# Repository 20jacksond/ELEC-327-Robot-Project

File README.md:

# ELEC-327-Robot-Project
Repository for the C code (for robot control), Python code (for computer vision), and associated PCB files and other design documents.

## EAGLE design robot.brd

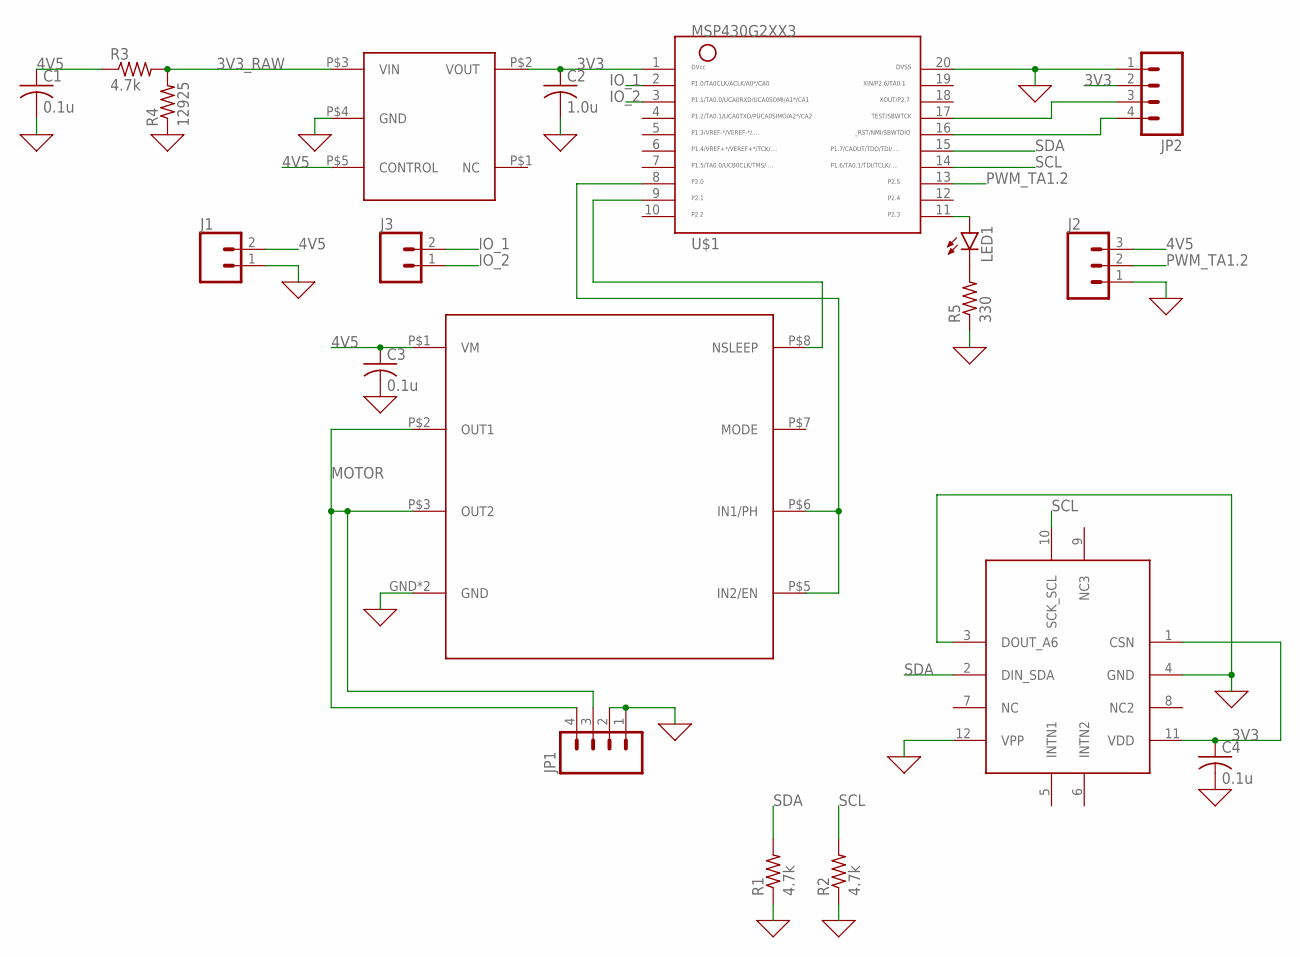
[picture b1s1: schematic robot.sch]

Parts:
C1, C3, C4: 0.1u; C0805
C2: 1.0u; C0805
J1, J3: CONN_02; 1X02
J2: CONN_03LOCK; 1X03_LOCK
JP1, JP2: HEADER_1X04LOCK; 1X04_LOCK
LED1: LED5MM
R1, R2, R3: 4.7k; R0805
R4: 12925; R0805
R5: 330; R0805
U$1: MSP430G2XX3PDIP; N20
U$2: DRV8220_H_BRIDGE
U$4: TCR2EF3V3
U$5: MC3419VFLGA-12; IC_MXC6655XA

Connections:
0: C1.2, C2.2, C3.2, C4.2, J1.1, J2.1, JP1.1, JP1.2, JP2.1, R1.1, R2.1, R4.1, R5.1, U$1.20, U$2.GND, U$2.P$4 (GND), U$4.P$4 (GND), U$5.3 (DOUT_A6), U$5.4 (GND), U$5.12 (VPP)
3V3: C2.1, C4.1, JP2.2, U$1.1, U$4.P$2 (VOUT), U$5.1 (CSN), U$5.11 (VDD)
3V3_RAW: R3.2, R4.2, U$4.P$3 (VIN)
4V5: C1.1, C3.1, J1.2, J2.3, R3.1, U$2.P$1 (VM), U$4.P$5 (CONTROL)
IO_1: J3.2, U$1.2
IO_2: J3.1, U$1.3
MOTOR: JP1.3, JP1.4, U$2.P$2 (OUT1), U$2.P$3 (OUT2)
unnamed: LED1.A, U$1.11
unnamed: U$1.9, U$2.P$8 (NSLEEP)
unnamed: LED1.K (C), R5.2
unnamed: U$1.8, U$2.P$5 (IN2/EN), U$2.P$6 (IN1/PH)
unnamed: JP2.3, U$1.17
unnamed: JP2.4, U$1.16
PWM_TA1.2: J2.2, U$1.13
SCL: R2.2, U$1.14, U$5.10 (SCK_SCL)
SDA: R1.2, U$1.15, U$5.2 (DIN_SDA)

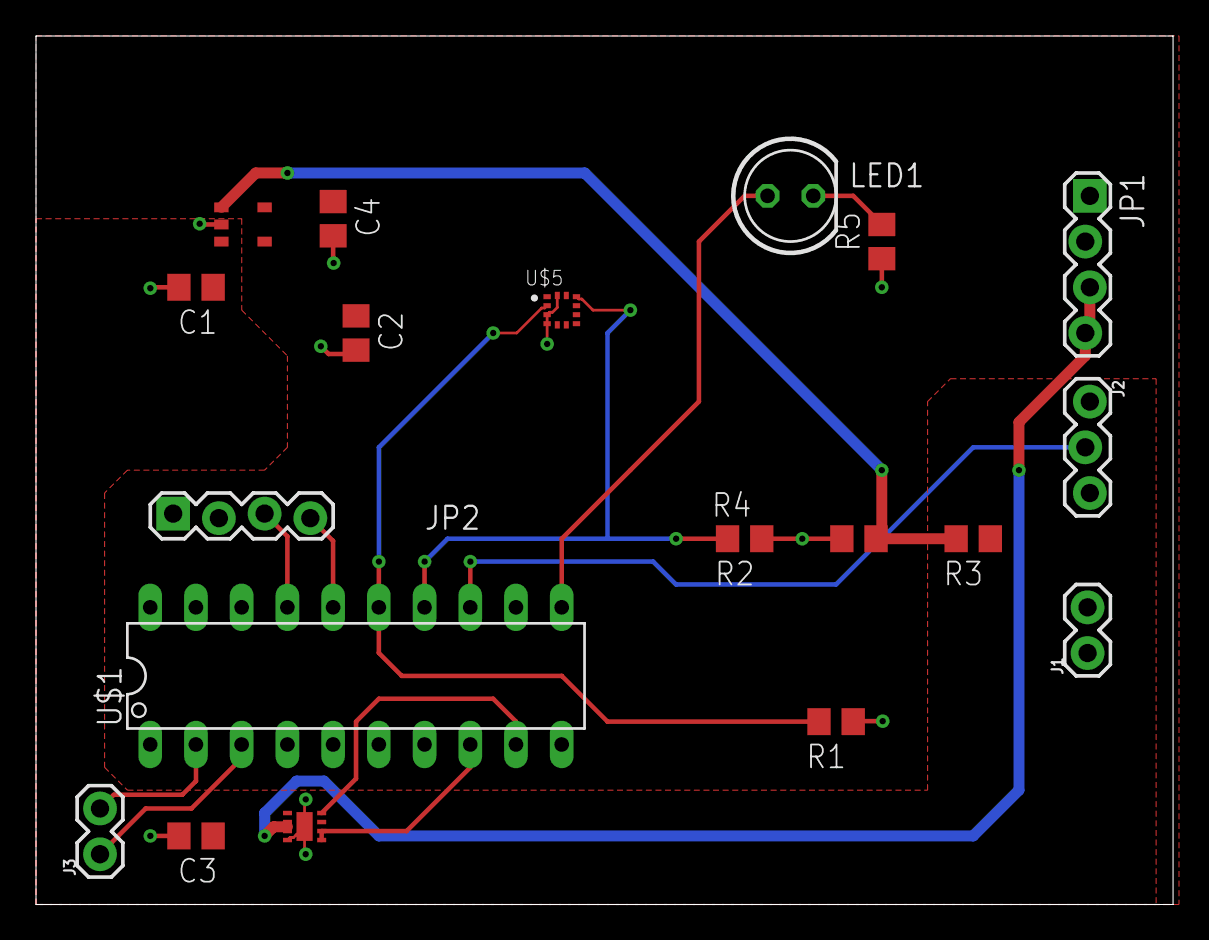
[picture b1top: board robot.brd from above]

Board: 2 copper layers, 63.2 x 48.2 mm, 19 parts (0 on the bottom side), 16 nets.

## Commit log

2023-04-06 Initial Commit. Contains Schematic for the robot's MSP430 control board.
2023-04-06 Initial commit of code for the robot project.
2023-04-10 Added brushed motor controllers and voltage regulator.
2023-04-11 Only need one more footprint for the servo motor controller. Began connecting components in the schematic.
2023-04-11 Added custom libraries.
2023-04-11 line identification code
2023-04-11 Schematic complete for review.
2023-04-12 Added board
2023-04-15 Added power planes to board and also added a resistor for the LED.
2023-04-16 added VIAs
2023-04-16 new added vias
2023-04-23 lines code while reading video from webcam (draft)
2023-04-24 Adding the STL files for 3D printing the chassis.
2023-04-24 set bbb output pins based on frames
2023-04-25 Added two-pin header to board for interface with BeagleBone.
2023-04-25 Commit not working :(
2023-04-25 updated code
2023-04-26 updated C code
2023-04-29 Updated code and added test code
2023-04-30 fixed blue threshold, check frames faster
2023-05-03 Added low power mode handling and PWM clock setup.

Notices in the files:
parts and their libraries:
SparkFun-Connectors: Licensing: Creative Commons ShareAlike 4.0 International - https://creativecommons.org/licenses/by-sa/4.0
